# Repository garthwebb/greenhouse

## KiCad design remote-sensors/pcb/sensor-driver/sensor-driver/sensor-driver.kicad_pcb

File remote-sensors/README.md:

# Remote sensors

Battery powered temp/humidity sensors for the greenhouse.

```
sensor-node ──ESP-NOW──▶ gateway-radio ──UART──▶ gateway-uplink ──WiFi/MQTT──▶ mosquitto (tiger-pi)
 (battery)               (fixed channel)          (WiFi client)                   ├─▶ greenhouse controller
                                                                                  └─▶ telegraf ─▶ InfluxDB
```

- **sensor-node** wakes every 5 minutes, reads an SHT4x, sends one ESP-NOW packet and sleeps. About 100ms awake per reading.
- **gateway-radio** only listens for ESP-NOW, on `ESPNOW_CHANNEL`. It never joins WiFi, so its channel never changes when UniFi switches channels or the uplink roams to another AP. It gives itself the fixed MAC `02:47:48:00:00:01`, so sensors don't need to be told its address.
- **gateway-uplink** is an ordinary WiFi client. It publishes each reading, retained, to `greenhouse/sensors/<sensor MAC>/state`:
  ```json
  {"id":"348518abcdef","temperature":74.12,"humidity":81.20,"battery_v":2.874,"battery_used_mah":412,"battery_pct":68.3,"rssi":-67,"seq":1234,"attempt":0,"missed":0,"ts":1760000000}
  ```
  - `temperature` is °F, matching the controller.
  - `attempt` is the number of failed sends before this one got through. `missed` is the number of readings the sensor gave up on entirely since its last delivered one.
  - `battery_v` is measured with the radio on (see [Battery monitoring](#battery-monitoring)). `battery_used_mah` and `battery_pct` come from the sensor's charge count.

## Hardware

All three use a Seeed XIAO ESP32-C3.

**Gateway:** two XIAOs powered from the same USB supply, wired together:

| gateway-radio | gateway-uplink |
|---|---|
| D6 (TX) | D7 (RX) |
| D7 (RX) | D6 (TX) |
| GND | GND |

**Sensor node:**

```
CR123A + ──┬──────────────▶ boost converter IN      boost OUT (3.3V) ──▶ XIAO 3V3
           │                                        boost GND ─────────▶ XIAO GND
          100k
           ├──────────────▶ XIAO A1
          100k   10nF A1 to GND
           │
         drain
  XIAO D2 ──▶ gate   2N7002 (or similar logic-level N-MOSFET)
          100k gate to GND
         source
           │
CR123A − ──┴──── GND
```

- **Sensor:** SHT45 on SDA (D4) / SCL (D5), with a 100nF cap across its supply.
- **Power:** a 3.3V boost converter with a low idle current, such as one built on a TPS61099 (about 1µA). A CR123A sits around 2.8–3.0V under load, below the ESP32-C3's 3.0V minimum, so it can't run the XIAO directly.
  - Feed the XIAO through its **3V3 pin, never its BAT pads.** The BAT pads go to a lithium-ion charger that would try to charge the CR123A whenever USB is plugged in.
  - **Take the battery out before plugging in USB** to flash it, so the USB supply and the battery aren't both feeding the 3.3V rail.
- **Battery divider:** 100k + 100k on the battery side of the boost converter, read on A1. A MOSFET on the low side, driven from D2, connects it only while the firmware reads it, so it draws nothing during sleep.
  - **The 100k gate pull-down is required.** D2 floats in deep sleep, and the pull-down keeps the divider off.
  - A1 rather than A0 because A0 is a boot strapping pin on the C3.
- The XIAO board itself draws ~40µA in deep sleep, which a bare ESP32-C3 module wouldn't. That's most of the power budget.

## Battery monitoring

The sensor reports two independent measures.

- **Voltage under load (`battery_v`).** A CR123A's resting voltage stays nearly flat until it's almost empty. Its voltage while the radio is drawing ~100mA sags more as it wears, so the firmware takes the reading with the radio on.
- **Charge used (`battery_used_mah`, `battery_pct`).** The firmware adds up an estimate of the charge used on every wake and every sleep.
  - The running total lives in RTC memory and survives deep sleep, brownouts and watchdog resets.
  - It only resets to zero on a power-on reset, which in practice means a battery was just put in.
  - If you put a *used* battery back in, the count will restart at zero and read too optimistic.
  - **Calibrate it once:** measure the battery current with a power profiler (or a µA-range meter), then set `SLEEP_CURRENT_UA` and `AWAKE_CURRENT_MA` in `platformio.ini`. The defaults (50µA asleep, 60mA awake) are estimates. `BATTERY_CAPACITY_MAH` defaults to 1300, the usable capacity of a CR123A down to where the boost converter gives out.

The controller flags a sensor as low when it drops below 15% remaining **or** 2.6V under load, whichever comes first. The voltage check catches a battery draining faster than the estimate expects. It logs a warning to syslog when a sensor crosses either threshold, and the `remote` WebSerial command marks it `(LOW BATTERY)`.

Rough battery life on one CR123A, reading and sending every 5 minutes: about 2 years.

## Outdoor housing

`enclosure/sensor_housing.py` generates a stacked-plate radiation shield sitting on a sealed pod for the battery and electronics. It writes STEP and STL files to `enclosure/out/`. It reads the driver board's outline and part positions straight from `pcb/sensor-driver/sensor-driver/sensor-driver.kicad_pcb`, so **rerun it whenever you change that board**. `assembly.step` shows the board, its battery holder, XIAO and Qwiic header in orange, to check fit. To regenerate:

```
pip install cadquery
python sensor_housing.py
```

The script stops with an error if a change makes something not fit, for example:
- the sensor board hitting the base
- the driver board or its tall parts not fitting in the pod
- the grommet landing on a tall part
- a screw that won't reach its insert

**How the shield blocks sun but not air:**
- Every plate is a 45° cone sloping down to the outside, stacked 10 mm apart.
- Each cone is 20 mm tall, twice the gap between plates, so there's no straight path for sunlight to reach the center.
- Air flows sideways through the 5.5 mm gaps between plates. Going much tighter starts to choke the airflow on still days.
- The base closes off the bottom, so the sensor can't see sunlit ground. The cable drops through an 8 mm hole at its apex.

**The pod:**
- **Lid:** an O-ring plug, held by three radial M3 screws through the pod wall into heat-set inserts in the plug, below the O-ring.
- **Driver board:** screws to two 3 mm standoffs on the lid (M2.5 heat-set inserts) at its H1/H2 mounting holes. The standoffs clear the trimmed through-hole leads of the battery holder and headers. The battery holder sits toward one side of the pod and the XIAO and Qwiic header toward the other. The holder's top clears the pod's top by 1.1 mm and the XIAO's USB-C by 4 mm.
- **Battery changes:** removing the lid's three radial screws pulls the lid out with the whole board on it.
- **Cable:** a 200 mm Qwiic / STEMMA QT cable (JST-SH plugs on both ends) runs from the sensor board, through the base's 8 mm hole, and into the pod through a 7.5 mm hole directly above the driver board's Qwiic header, so the cable drops straight in. Both holes pass the plug, so the shield and pod come apart by unplugging both ends; nothing has to be desoldered.
- **Sealing the cable:** a split TPU grommet snaps around the cable and presses into the pod's hole from outside, with a barb that catches underneath. The base cone keeps rain off it.
  - The grommet's bore is sized for a flat four-wire cable, 4.2 × 1.2 mm. Measure yours and adjust `CABLE_W` and `CABLE_T` if it differs.
- **Shield screws:** they go into heat-set inserts in blind holes in the pod top, so nothing pierces the sealed space.
- **Condensation:** a small adhesive vent membrane on the lid helps avoid it if you see any.

**Print** in white ASA or PETG (PLA sags in sun). No supports needed; every part is exported in its print orientation.
- 1× `base`
- 3× `plate`
- 1× `cap` (exported upside down, flat side on the bed)
- 1× `pod` (exported upside down, top on the bed)
- 1× `pod_lid`
- 1× `grommet`, in **TPU** (95A or similar), flange down on the bed

**Hardware:**
- 3× M3 × 70 mm socket head screws (shield to pod)
- 3× M3 × 6 mm screws (lid)
- 6× M3 heat-set inserts, 4 mm long (3 in the pod top, 3 in the lid plug)
- 2× M2.5 heat-set inserts and 2× M2.5 × 6 mm screws (driver board to lid standoffs)
- 1× O-ring, 2 mm cross-section, about 55 mm ID
- 200 mm Qwiic / STEMMA QT cable, and two JST-SH 4-pin headers: SM04B-SRSS-TB (side entry) on the sensor board, SM04B or BM04B (vertical) on the controller board

**Sensor PCB:** designed for 15 × 15 mm, 1.6 mm thick (up to 20 mm long still fits). The side edges slide up into two slotted rails hanging from the cap.
- The rails hold only the outer 1.5 mm of each side edge, over the top 6 mm. Keep components out of those strips, and don't let anything stick up past the top edge.
- Put the sensor below the rails, with its 0.1µF cap next to its VDD pin, and a side-entry JST-SH header (SM04B-SRSS-TB) on the bottom edge facing down, so the cable drops straight to the cable hole. Qwiic pinout: black GND, red 3.3V, blue SDA, yellow SCL. Change `PCB_W`, `PCB_T`, `PCB_LEN` and `RAIL_LEN` in the script to fit a different board. A drop of glue or a snug fit holds it in.

**Overall:** 64 mm diameter, 108.5 mm tall. The cap's two M4 holes are for mounting to a bracket or arm.

## Channel

`ESPNOW_CHANNEL` (default 11) is set in `code/include/remote_sensor_protocol.h`. Sensors and gateway-radio must be flashed with the same value. Pick a 2.4GHz channel the UniFi APs aren't using.

## Building

From `code/`:

```
pio run -e sensor-node -t upload
pio run -e gateway-radio -t upload
pio run -e gateway-uplink -t upload
```

- `sensor-node-debug` reads every 30s and prints to USB serial.
- `gateway-uplink` uses the controller's `controller/code/src/wifi-info.h` for WiFi credentials, and the `embedded-shared` libraries for WiFi and syslog.
- All three must run the same packet version (`SENSOR_PACKET_VERSION`); the gateway radio rejects packets from a different version.

## tiger-pi

1. Install the broker:
   ```
   sudo apt install mosquitto
   ```
2. Copy `tiger-pi/mosquitto-greenhouse.conf` to `/etc/mosquitto/conf.d/greenhouse.conf`, then restart mosquitto.
3. Copy `tiger-pi/telegraf-greenhouse-sensors.conf` to `/etc/telegraf/telegraf.d/`, then restart telegraf. Read the note at the top of that file if this Telegraf already writes to other outputs.

Readings land in the `greenhouse` database:
- measurement: `weather`
- tags: `device=greenhouse-remote`, `sensor_id=<MAC>`
- fields: `temperature`, `humidity`, `battery_v`, `battery_used_mah`, `battery_pct`, `rssi`, `seq`, `attempt`, `missed`

To watch the raw stream:

```
mosquitto_sub -h tiger-pi.local -t 'greenhouse/#' -v
```

## Controller

The controller subscribes to `greenhouse/sensors/+/state` through `RemoteSensors` (`controller/code/lib/RemoteSensors`). It keeps the latest reading from each sensor in `SENSORS->remote->readings()`. The `remote` WebSerial command lists them with their age and battery state. Readings older than 15 minutes are marked stale.

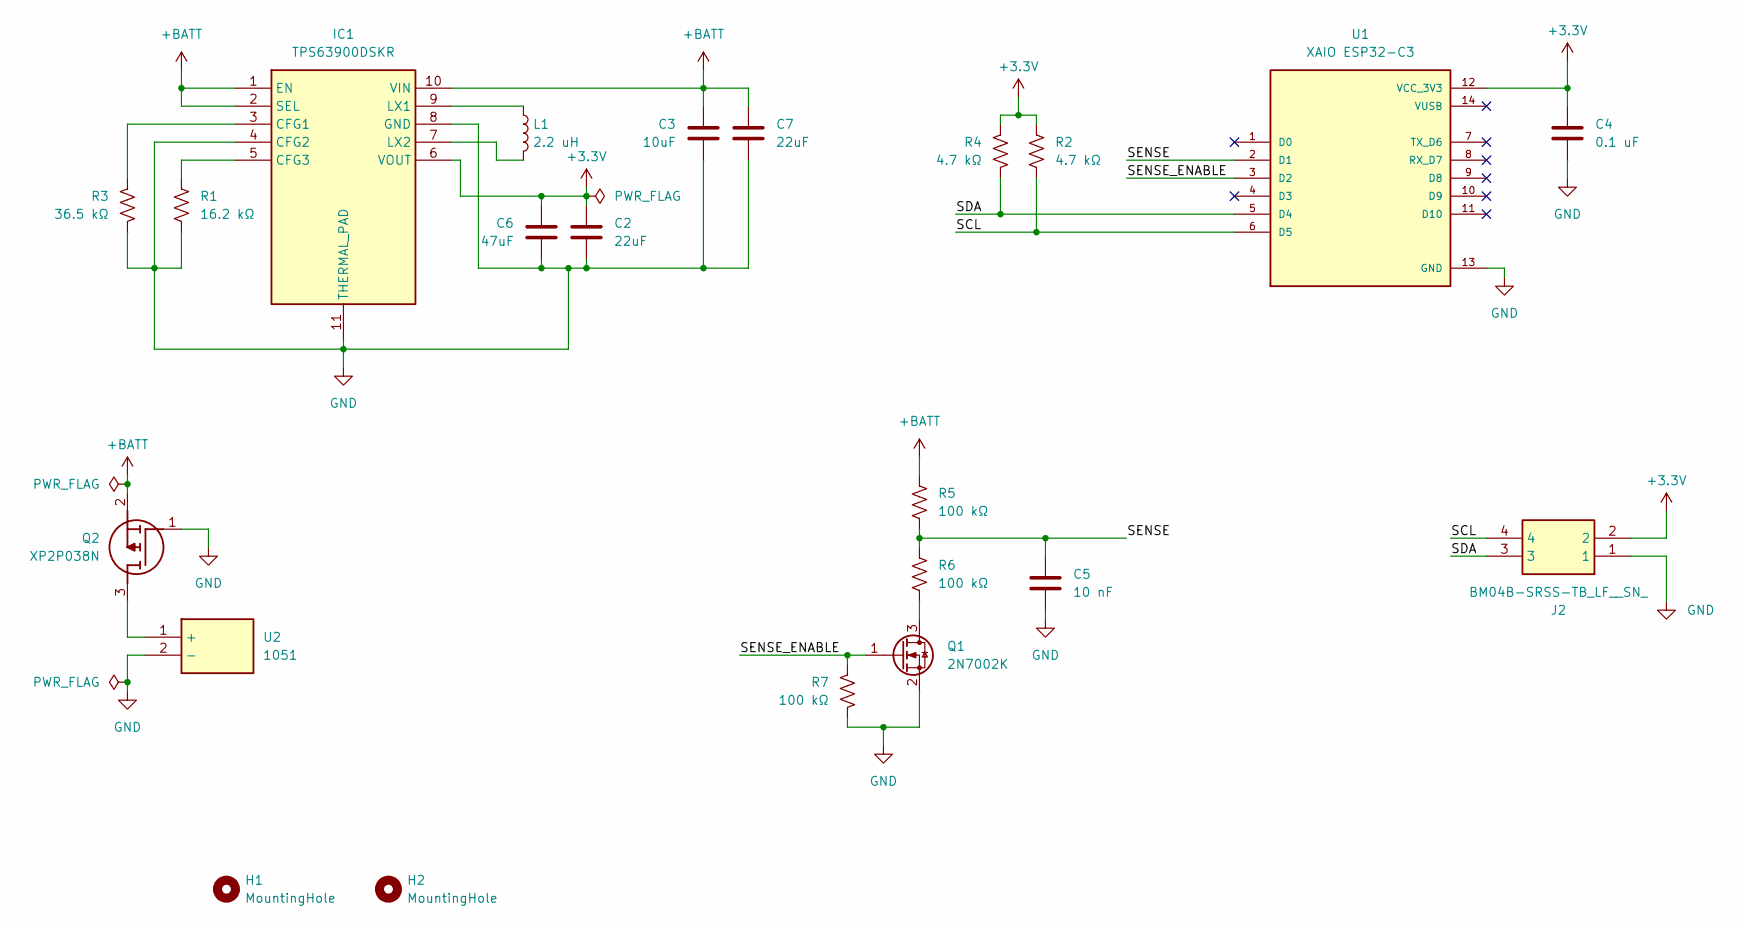
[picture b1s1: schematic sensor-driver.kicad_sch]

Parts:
C2, C7: 22uF; C_0805_2012Metric_Pad1.18x1.45mm_HandSolder
C3: 10uF; C_0805_2012Metric_Pad1.18x1.45mm_HandSolder
C4: 0.1 uF; C_0805_2012Metric_Pad1.18x1.45mm_HandSolder
C5: 10 nF; C_1206_3216Metric_Pad1.33x1.80mm_HandSolder
C6: 47uF; C_1206_3216Metric_Pad1.33x1.80mm_HandSolder
H1, H2: MountingHole; MountingHole_2.7mm_M2.5
IC1: TPS63900DSKR; SON50P250X250X80-11N-D; Mouser Part Number 595-TPS63900DSKR
J2: BM04B-SRSS-TB_LF__SN_; BM04B-SRSS-TB_LFSN_; Mouser Part Number N/A
L1: 2.2 uH; L_1008_2520Metric_Pad1.43x2.20mm_HandSolder
Q1: 2N7002K; SOT-23
Q2: XP2P038N; SOT95P230X109-3N; Manufacturer_Part_Number XP2P038N
R1: 16.2 kΩ; R_0805_2012Metric_Pad1.20x1.40mm_HandSolder
R2, R4: 4.7 kΩ; R_0805_2012Metric_Pad1.20x1.40mm_HandSolder
R3: 36.5 kΩ; R_0805_2012Metric_Pad1.20x1.40mm_HandSolder
R5, R6, R7: 100 kΩ; R_0805_2012Metric_Pad1.20x1.40mm_HandSolder
U1: XAIO ESP32-C3; MODULE_113991054; PARTREV 23/05/2022
U2: 1051; Mouser Part Number 534-1051

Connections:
+3.3V: C2.1, C4.1, C6.1, IC1.6 (VOUT), J2.2, R2.2, R4.2, U1.12 (VCC_3V3)
+BATT: C3.1, C7.1, IC1.1 (EN), IC1.2 (SEL), IC1.10 (VIN), Q2.2 (S), R5.2
/SCL: J2.4, R2.1, U1.6 (D5)
/SDA: J2.3, R4.1, U1.5 (D4)
/SENSE: C5.1, R5.1, R6.2, U1.2 (D1)
/SENSE_ENABLE: Q1.1 (G), R7.2, U1.3 (D2)
GND: C2.2, C3.2, C4.2, C5.2, C6.2, C7.2, IC1.4 (CFG2), IC1.8 (GND), IC1.11 (THERMAL_PAD), J2.1, Q1.2 (S), Q2.1 (G), R1.1, R3.1, R7.1, U1.13 (GND), U2.2 (-)
unnamed: IC1.3 (CFG1), R3.2
unnamed: IC1.5 (CFG3), R1.2
unnamed: IC1.9 (LX1), L1.1
unnamed: IC1.7 (LX2), L1.2
unnamed: Q1.3 (D), R6.1
unnamed: Q2.3 (D), U2.1 (+)

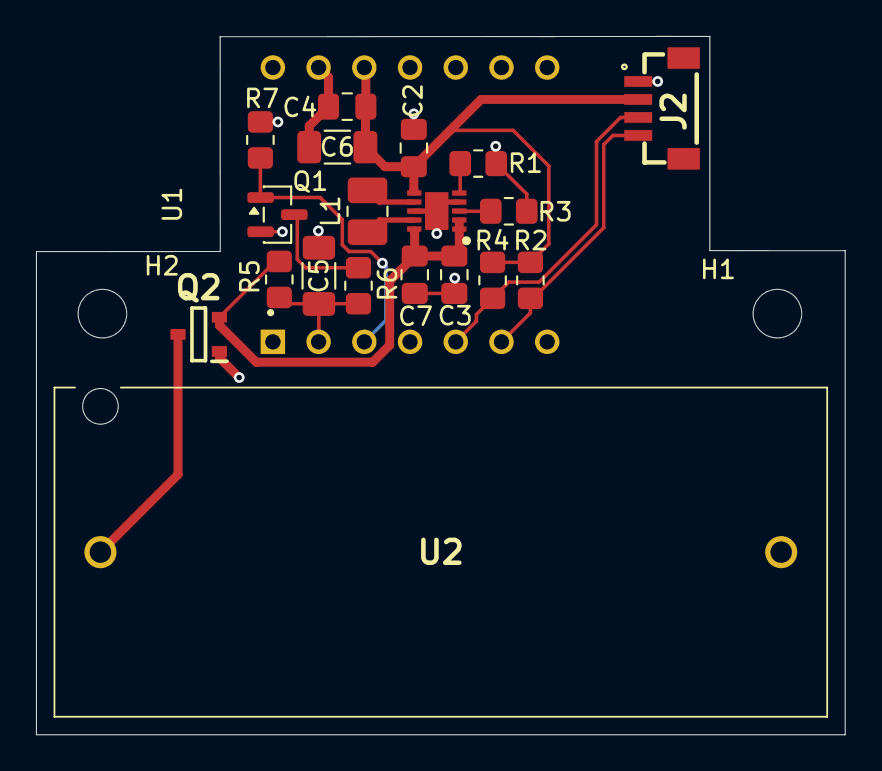
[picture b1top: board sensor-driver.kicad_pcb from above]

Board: 2 copper layers, 44.9 x 38.8 mm, 22 parts (0 on the bottom side), 13 nets.

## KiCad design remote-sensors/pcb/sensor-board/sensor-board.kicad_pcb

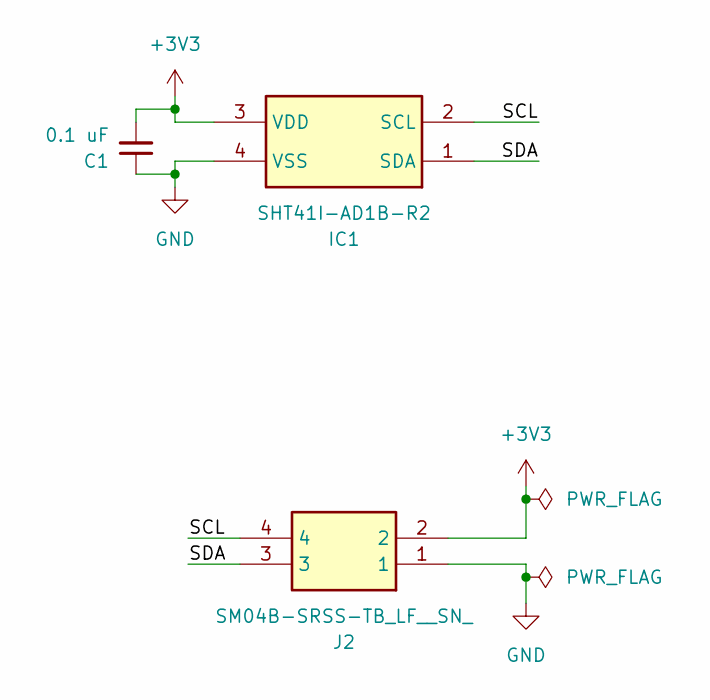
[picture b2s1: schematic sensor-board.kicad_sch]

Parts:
C1: 0.1 uF; C_0805_2012Metric_Pad1.18x1.45mm_HandSolder
IC1: SHT41I-AD1B-R2; Sensirion_DFN-4_1.5x1.5mm_P0.8mm_SHT4x_NoCentralPad; Mouser Part Number 403-SHT41I-AD1B-R2
J2: SM04B-SRSS-TB_LF__SN_; SM04B-SRSS-TB_LFSN_; Mouser Part Number 306-SM04BSRSSTBLFSN

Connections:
+3V3: C1.2, IC1.3 (VDD), J2.2
/SCL: IC1.2 (SCL), J2.4
/SDA: IC1.1 (SDA), J2.3
GND: C1.1, IC1.4 (VSS), J2.1

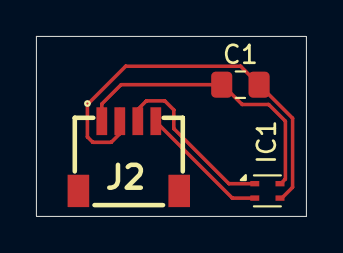
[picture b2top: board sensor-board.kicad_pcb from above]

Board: 2 copper layers, 15.0 x 10.0 mm, 3 parts (0 on the bottom side), 4 nets.

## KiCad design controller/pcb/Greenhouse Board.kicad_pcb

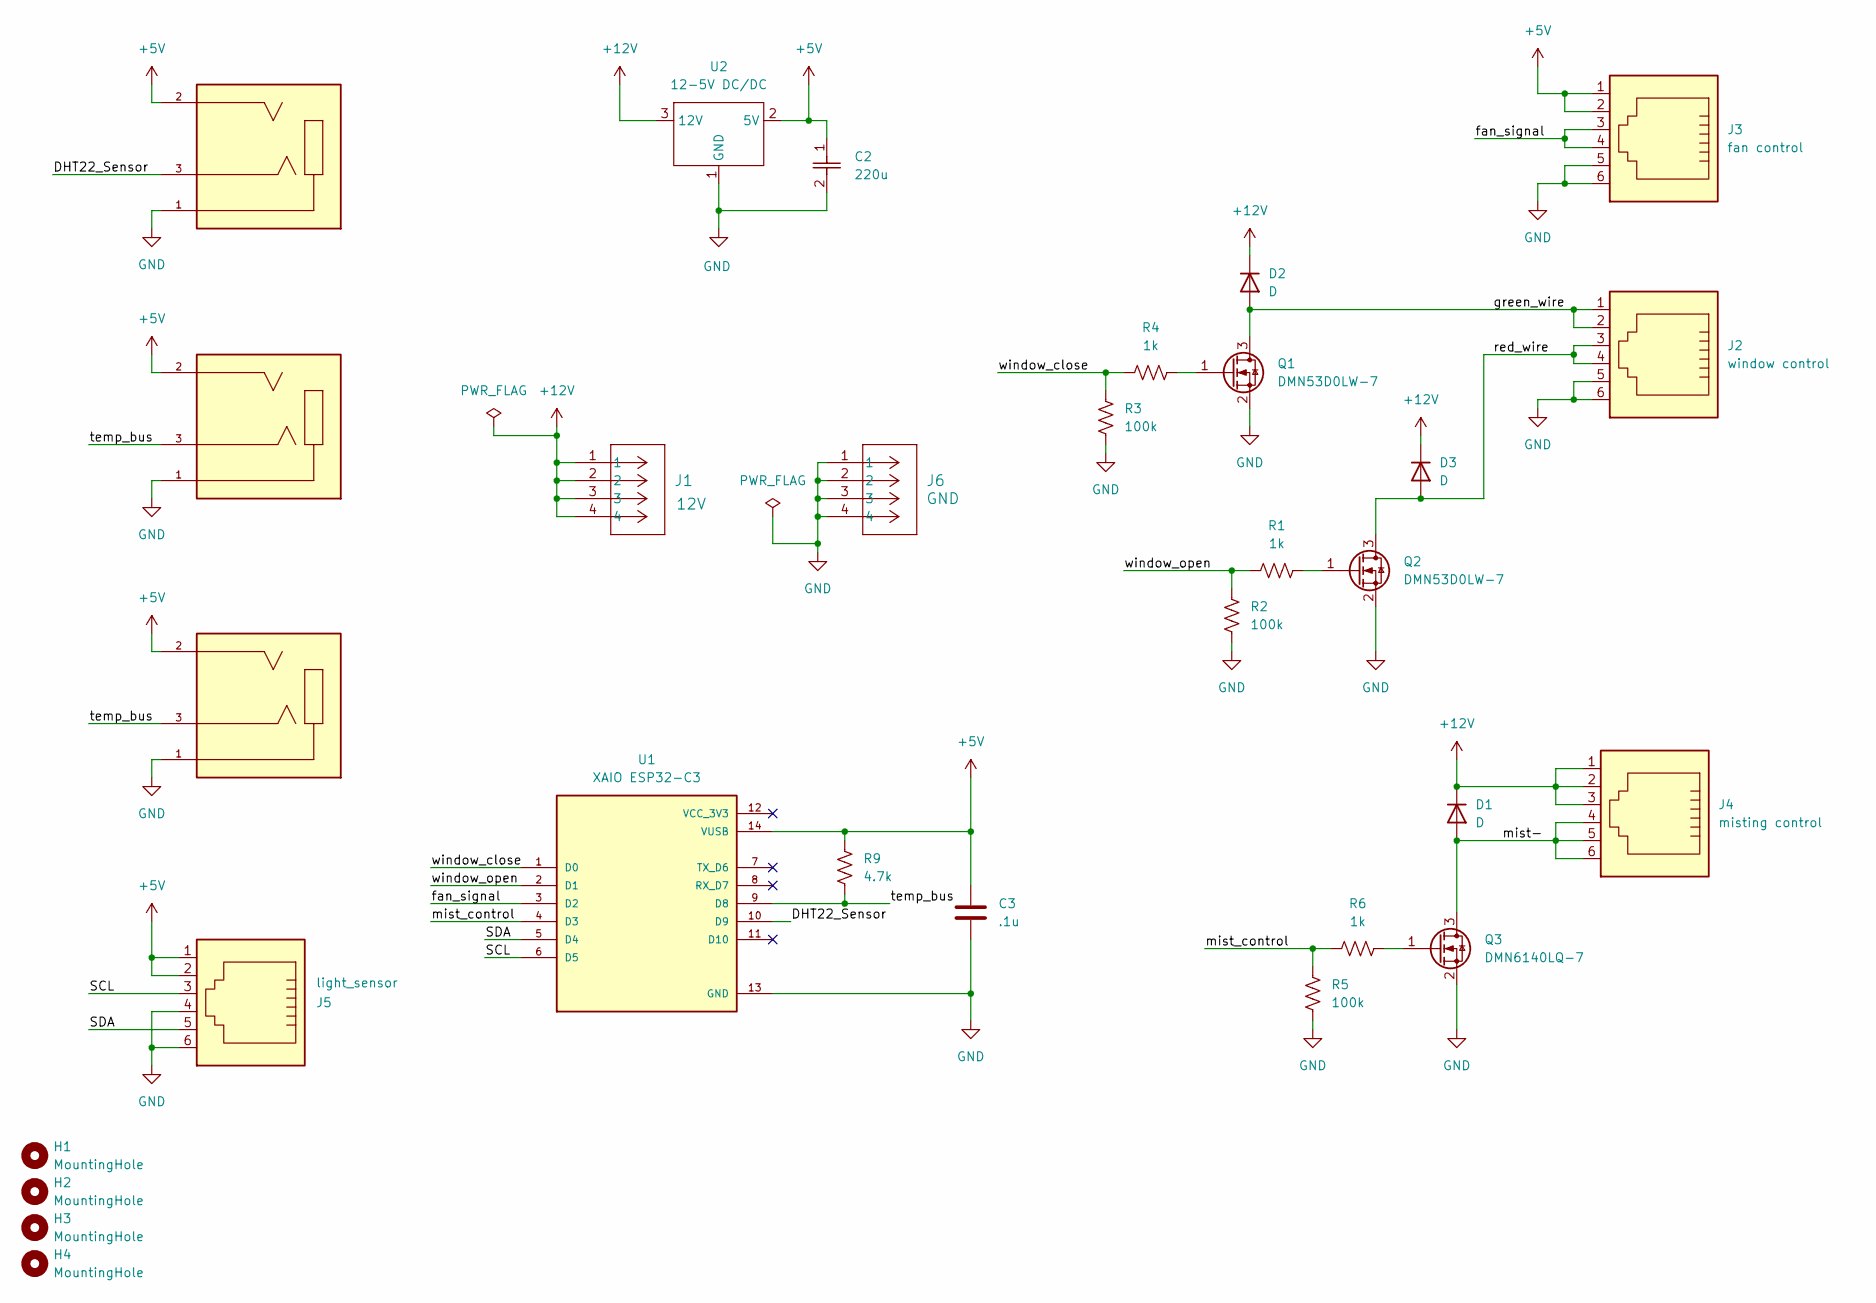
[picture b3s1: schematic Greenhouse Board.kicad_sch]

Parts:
C2: 220u; CAP_SP-CAP_SR_PAN
C3: .1u; C_0805_2012Metric
D1, D2, D3: D; SOD323_DIO
H1, H2, H3, H4: MountingHole; MountingHole_3.2mm_M3
J1: 12V; screw-terminal-CONN4_TB002-500_787x299_CUD
J2: window control; RJ11-RA; PARTREV N
J3: fan control; RJ11-RA; PARTREV N
J4: misting control; RJ11-RA; PARTREV N
J5: light_sensor; RJ11-RA; PARTREV N
J6: GND; screw-terminal-CONN4_TB002-500_787x299_CUD
J7: T+H sensor; 1_8jack-CUI_SJ2-35853A-SMT-TR; PARTREV 1.04
J8: temp sensor 1; 1_8jack-CUI_SJ2-35853A-SMT-TR; PARTREV 1.04
J9: temp sensor 2; 1_8jack-CUI_SJ2-35853A-SMT-TR; PARTREV 1.04
Q1, Q2: DMN53D0LW-7; SOT-323_SC-70_Handsoldering
Q3: DMN6140LQ-7; SOT-323_SC-70_Handsoldering
R1, R4, R6: 1k; R_0805_2012Metric_Pad1.20x1.40mm_HandSolder
R2, R3, R5: 100k; R_0805_2012Metric_Pad1.20x1.40mm_HandSolder
R9: 4.7k; R_0805_2012Metric_Pad1.20x1.40mm_HandSolder
U1: XAIO ESP32-C3; MODULE_113991054; PARTREV 23/05/2022
U2: 12-5V DC/DC; Power Module 6-pin

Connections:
+5V: C2.1, C3.1, J3.1, J3.2, J5.1, J5.2, J7.2, J8.2, J9.2, R9.1, U1.14 (VUSB), U2.2 (5V)
+12V: D1.1 (K), D2.1 (K), D3.1 (K), J1.1, J1.2, J1.3, J1.4, J4.1, J4.2, J4.3, U2.3 (12V)
/DHT22_Sensor: J7.3, U1.10 (D9)
/SCL: J5.3, U1.6 (D5)
/SDA: J5.5, U1.5 (D4)
/fan_signal: J3.3, J3.4, U1.3 (D2)
/green_wire: D2.2 (A), J2.1, J2.2, Q1.3 (D)
/mist-: D1.2 (A), J4.4, J4.5, J4.6, Q3.3 (D)
/mist_control: R5.1, R6.1, U1.4 (D3)
/red_wire: D3.2 (A), J2.3, J2.4, Q2.3 (D)
/temp_bus: J8.3, J9.3, R9.2, U1.9 (D8)
/window_close: R3.1, R4.1, U1.1 (D0)
/window_open: R1.1, R2.1, U1.2 (D1)
GND: C2.2, C3.2, J2.5, J2.6, J3.5, J3.6, J5.4, J5.6, J6.1, J6.2, J6.3, J6.4, J7.1, J8.1, J9.1, Q1.2 (S), Q2.2 (S), Q3.2 (S), R2.2, R3.2, R5.2, U1.13 (GND), U2.1 (GND)
unnamed: Q1.1 (G), R4.2
unnamed: Q2.1 (G), R1.2
unnamed: Q3.1 (G), R6.2

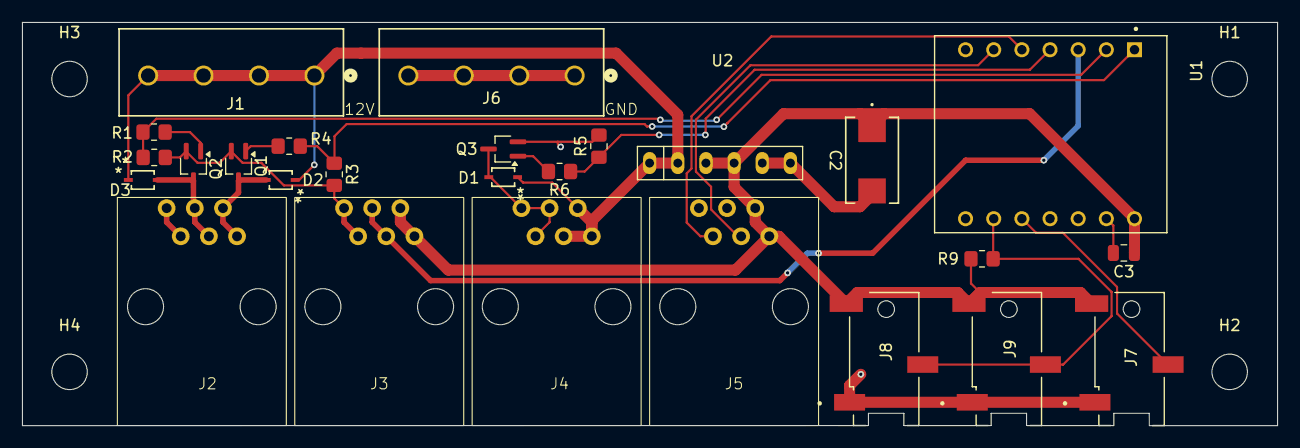
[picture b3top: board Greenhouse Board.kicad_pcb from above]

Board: 2 copper layers, 113.2 x 36.4 mm, 30 parts (0 on the bottom side), 17 nets.

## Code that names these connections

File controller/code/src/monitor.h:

#ifndef MONITOR_H
#define MONITOR_H

#include "wifi-info.h"

#include "FanControl.h"
#include "WindowControl.h"
#include "MistControl.h"

#include "TempHumiditySensor.h"
#include "TempSensor.h"
#include "LightSensor.h"
#include "RemoteSensors.h"

//----------------------------------------------------
// Defines

#ifndef HOSTNAME
#define HOSTNAME "greenhouse-esp32"
#endif

#ifndef DEVICE
#define DEVICE "ESP32"
#endif

#define SERIAL_SPEED 115200

struct ControlObjects {
    FanControl *fan;
    WindowControl *window;
    MistControl *mist;
};

struct SensorObjects {
    TempHumiditySensor *temphumid;
    SensorHandler *temp;
    LightSensor *light;
    RemoteSensors *remote;
};

//---- GPIO Pins : Set defaults but defer to the platformio file for specific boards for pin numbers

// Main temp+humidity sensor
#ifndef DT22_PIN
#define DT22_PIN 13
#endif

#ifndef WINDOW_OPEN_PIN
#define WINDOW_OPEN_PIN 33
#endif

#ifndef WINDOW_CLOSE_PIN
#define WINDOW_CLOSE_PIN 32
#endif

#ifndef FAN_CONTROL_PIN
#define FAN_CONTROL_PIN 25
#endif

#ifndef MIST_CONTROL_PIN
#define MIST_CONTROL_PIN 25
#endif

//---- Temperature Sensors
#ifndef ONE_WIRE_BUS_PIN
#define ONE_WIRE_BUS_PIN D8
#endif

//---- How to access external settings
#ifndef SETTINGS_HOST
#define SETTINGS_HOST "tigerbackup.local"
#endif
#ifndef SETTINGS_PORT
#define SETTINGS_PORT 80
#endif
#ifndef SETTINGS_PATH
#define SETTINGS_PATH "/greenhouse/settings.json"
#endif

// Syslog server connection info
#define SYSLOG_SERVER "tigerbackup.local"
#define SYSLOG_PORT 514
#define APP_NAME "env-control"

#define ENABLE_ADMIN_ACCESS true

//-- Influx DB
//#define INFLUXDB_URL "http://tiger-pi.local:8086"
#define INFLUXDB_URL "http://192.168.3.88:8086"
#define INFLUXDB_DB "greenhouse"
#define TELEMETRY_DB "telemetry"

//-- MQTT broker for the battery powered remote sensors
#ifndef MQTT_HOST
#define MQTT_HOST "192.168.3.88"
#endif
#ifndef MQTT_PORT
#define MQTT_PORT 1883
#endif

// Quickly enable/disable infux logging.  Can be controlled via platformio.ini
#ifndef LOG_TO_INFLUX
#define LOG_TO_INFLUX true
#endif

// Quickly enable/disable telemetry logging via syslog.  Can be controlled via platformio.ini
#ifndef LOG_TELEMETRY
#define LOG_TELEMETRY true
#endif

// Whether to log to a central syslog server
#ifndef LOG_TO_SYSLOG
#define LOG_TO_SYSLOG true
#endif

// Enable/disable Arduino OTA support in firmware.
#ifndef ENABLE_OTA_UPDATE
#define ENABLE_OTA_UPDATE true
#endif

// OTA listener is command-gated and disabled by default.
#ifndef OTA_LISTENER_ENABLED_BY_DEFAULT
#define OTA_LISTENER_ENABLED_BY_DEFAULT false
#endif

// OTA listener port used by ArduinoOTA.
#ifndef OTA_PORT
#define OTA_PORT 3232
#endif

// Optional OTA password used by PlatformIO espota uploads.
#ifndef OTA_PASSWORD
#define OTA_PASSWORD ""
#endif

// Temp above which we always want the windows open
#define ALWAYS_OPEN_TEMP_F (TARGET_TEMP_F + 15)
// Temp below witch we always want the windows closed
#define ALWAYS_CLOSE_TEMP_F (TARGET_TEMP_F - 5)

#define ALWAYS_FAN_TEMP_F (TARGET_TEMP_F + 10)
#define ALWAYS_NO_FAN_TEMP_F (TARGET_TEMP_F + 5)

// Time in seconds between collecting data
#define COLLECTION_PERIOD_S (1 * 60)
#define COLLECTION_PERIOD_MS (1000 * COLLECTION_PERIOD_S)

// How often to monitor the state of the system; should be short but not zero
#define MONITOR_PERIOD_S (1 * 5)
#define MONITOR_PERIOD_MS (1000 * MONITOR_PERIOD_S)

// Send a heartbeat every 60 minutes to the logger
#define HEARTBEAT_PERIOD_S (60 * 60)
#define HEARTBEAT_PERIOD_MS (1000 * HEARTBEAT_PERIOD_S)

// Set a short watchdog timer
#define WDT_TIMEOUT_S 120

#endif

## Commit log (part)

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2022-03-31 Adding new sketch
2022-04-01 FIrst version of this file
2024-06-07 Checkpoint some changes to history
2024-06-07 Update to move Adruido project to VSCode project, plus clean up
    * moved some components to libraries
    * improved async process handling like window opening
2025-01-22 Add two new libraries and a place to test out code
    * ClimateControl - encapsulates reading the temp/humiditiy and what decisions to make based on that
    * Logger - Log to an external syslog server
2025-01-22 Rename the main code file, also split things out to libraries.
2025-01-22 Tidy up the platform file, add experiments and a common config section
2025-01-22 Several refactoring changes
2025-04-02 Ignore autosave files
2025-04-02 Checkpoint changes before updating design
2025-04-07 Create a watchdog timer, as well as set a hostname for this device.
2025-04-10 Introduce 1/8" jack components and add additional inputs and outputs
2025-04-10 Send a message to syslog when datalogging is enabled/disabled.
2025-04-11 Don't block in the main loop. Continuously handle all events and conditionally log to influx when the collection period is up.
2025-04-11 Move the watchdog timer to after all the setup and shorten its TTL. Also introduce an Telemetry class, but keep it commented out for the moment.
2025-04-11 Handle wifi disconnection better. Make sure the rest of the control code can still run even if wifi is down.
2025-04-11 Add telemetry logging
2025-04-11 Get rid of debugging return
2025-04-11 Fix some indendtation
2025-04-12 Extracted come common libaries and now including them back as submodules.
2025-04-12 Forgot to add lib dir for new dependencies
2025-04-12 Only have one thing that represents the name of this device on the network.
2025-06-21 Added libraries to monitor a different type of temperature sensor, a light sensor, and toggle a misting system. This new functionality is tested within the test-new-pcb file and platformio.ini profil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
2025-06-21 Updates to the PCB to expand its inputs/outputs
2025-06-21 Added and tested a settings library, to grab a json file from the NAS on the network that will supply control values for the greenhouse. All values will have local defaults..
2025-07-12 Sending more objects into AdminAccess so that its commands have access to more data.
2025-07-12 Moving all of the control logic out of the main monitor.cpp and into this lib to keep it contained and in one place.
2025-07-12 Added logging, and error checking for the HTTP connection. Also addressed some memory leaks with the _doc object reuse. Also resetting the HTTP connection on every monitor (happens once a minute) so 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
2025-07-12 Some clean up on variable names, and added some helper functions
2025-07-12 Genericized the handling of points a bit to accomodate additional different types of data.
2025-07-12 Handle not finding the light sensor. Mainly to allow the code to keep running while we're testing and don't have everything connected.
2025-07-12 Also log missing light sensors to syslog
2025-07-12 Clean up of variable names and adding helper functions
2025-07-12 Reuse the last readings from this sensor if a reading can't be made instead of returning zero. Zero gets logged and it looks like the values jump around on the graph when really there's no data.
2025-07-12 Rearrage this header
2025-07-12 Update private variables names, and add some helper functions
2025-07-12 Moved control and decision making to the ClimateControl object. Also bundle controls into a ControlObjects object and sensors into a SensorObjects object.
2025-07-12 Fold the experiment settings into a production config, but keeping a teting host and device name while we do integration testing.
2025-07-12 Small settings change. Not actuallty sure what the 103 to 0 change was, probably bumped something in the UI, but lets just keep it.
2025-07-15 An extra "-1" in an array index was causing kernel panics as the value it was subtracting from could be zero, and thus try to access index -1. This was causing the esp32 to reboot every 60 minutes as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
    Also did some standarization of names, and updated a logging method.
2025-08-07 Committing changes to TempHumidity sensor before completely swapping out the code to instead run with the AHT20
2025-08-25 Updated the Temp/Humidity sensor to an i2c version that does not suffer from the timing/interrupt issues that the other did. This fixed things, so installed the new controller, updated it's name to n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
2025-08-25 Helper function added to track whether the temp is currently rising or falling. The controller was opening windows because it anticipated it would reach the limit soon, but then immediately closed be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
2025-08-25 Add a type field to the event metrics to help qualify them. Also add more debugging output when a pint write fails. Reloated the admin access start up method to earlier in the process.
2025-08-25 Make the light sensor less sensitive since it will get bright in the greenhouse
2025-08-25 Incerase the heartbeat, remove some of the debugging messages.
